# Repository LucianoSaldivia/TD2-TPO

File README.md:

# TD2-TPO
 Proyecto Emulador de Chip8 para Técnicas Digitales 2

|          Tarea           | Responsable  | Estado |
|:-------------------------|:------------:|:------:|
|        Diseño PCB        |  LL y Willy  |   -    |
|      Diseño Carcaza      |     Fran     |   -    |
|         Pantalla         |      LL      |   -    |
|            SD            |    Luchos    |   -    |
|      Instrucciones       | Fran, Luchos |   +    |
|          Armado          |      LL      |   -    |
|     TDS y estructura     |      LS      |   T    |
|      Documentacion       |  el guilardo |   -    |
| Interfaz seleccion juego |    Luchos    |   -    |

- Estados de Tareas:
  - "-"	-> Tarea en proceso
  - "+"	-> Tarea codeada, no testeada	
  - "T"	-> Tarea testeada, no integrada
  - "I"	-> Tarea integrada

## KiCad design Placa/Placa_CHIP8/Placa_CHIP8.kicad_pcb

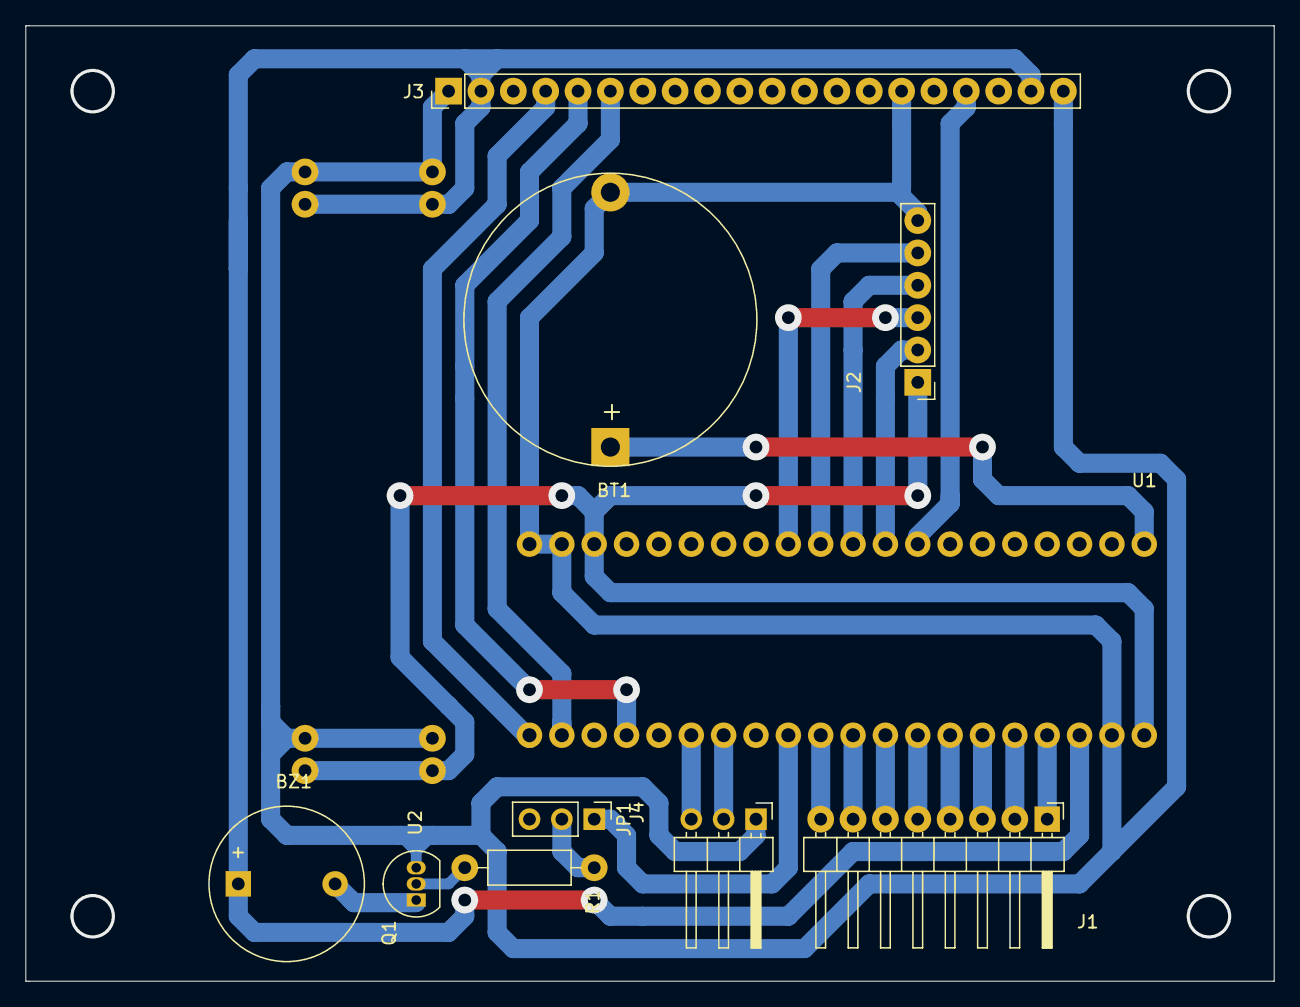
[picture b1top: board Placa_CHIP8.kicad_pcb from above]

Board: 2 copper layers, 98.0 x 75.0 mm, 11 parts (0 on the bottom side), 26 nets.

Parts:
BT1: Battery_Holder_CR2032; BatteryHolder_Keystone_103_1x20mm
BZ1: Buzzer; Buzzer_12x9.5RM7.6
J1: Conn_01x08_Male-Teclado-Matricial; PinHeader_1x08_P2.54mm_Horizontal
J2: Conn_01x06_Female-SD; PinHeader_1x06_P2.54mm_Vertical
J3: Conn_01x20_Female_LCD; PinHeader_1x20_P2.54mm_Vertical
J4: Conn_01x03_Male-UART; PinHeader_1x03_P2.54mm_Horizontal
JP1: Jumper; PinHeader_1x03_P2.54mm_Vertical
Q1: BC337; TO-92_Inline
R1: 10KΩ; R_Axial_DIN0207_L6.3mm_D2.5mm_P10.16mm_Horizontal
U1: STM32F103C8Tx; Blue_Pill
U2: Fuente

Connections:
+3V3: J2.1, U1.18, U1.40, U2.1
+5V: BZ1.1, J3.2, J3.19, U1.38, U2.3
+BATT: BT1.1, U1.1
/Buzzer: JP1.1, U1.29
/C1: J1.5, U1.33
/C2: J1.6, U1.32
/C3: J1.7, U1.31
/C4: J1.8, U1.30
/F1: J1.1, U1.37
/F2: J1.2, U1.36
/F3: J1.3, U1.35
/F4: J1.4, U1.34
/LCD_CLK: J3.6, U1.22
/LCD_CS: J3.4, U1.21
/LCD_MOSI: J3.5, U1.24
/LCD_RST: J3.17, U1.8
/RX_1: J4.2, U1.27
/SD_CLK: J2.4, U1.10
/SD_CS: J2.2, U1.9
/SD_MISO: J2.5, U1.11
/SD_MOSI: J2.3, U1.12
/TX_1: J4.3, U1.26
GND: BT1.2, J2.6, J3.1, J3.15, J3.20, J4.1, Q1.3, U1.19, U1.20, U1.39, U2.2, U2.4
unnamed: BZ1.2, Q1.1
unnamed: JP1.2, R1.2
unnamed: Q1.2, R1.1

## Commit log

2021-09-04 Primer Commit - Repo mudado
2021-09-05 [No testeado] Scheduler implementado como "objeto"
2021-09-07 Scheduler Testeado con dos tareas de ejemplo
    Se configuran las tareas con Período (en Ciclos Secundarios) y Offset (en micro segundos).
    Las tareas deben tener como parámetro void*, ejemplo:
    <task_type> <task_name>( void *p );
2021-09-15 Tareas / Responsables
2021-09-15 CHIP8 e instrucciones
    Implementacion de la estructura del CHIP8 y las instrucciones asociadas al mismo
2021-09-15 Estados de tareas
2021-09-15 Estado de Tareas -> Formato
2021-09-16 LCD GRAFICO & SD
    LCD grafico andando bien
    SD compila ok falta probar con una sd porque no tengo todavia
    Hay que cambiar SPI1 a SPI2
    Verificar TDS
2021-09-20 Agrego LCD Grafico, Teclado matricial y SD
    LCD GRAFICO OK -> Funcionando TIM4
    TECLADO MATRICIAL OK
    SD-> Resolviendo mis problemas con alarcon
2021-09-20 Cambio de lugar algunas cosas
2021-09-21 Agrego proyecto SD - Esta andando
2021-09-23 Agrego Intento de CHIP8
2021-09-23 Agrego configuracion HWD CHIP 8
2021-09-23 Terminar de resolver tema pantalla
2021-09-23 Graficar()->Andando
    Habría que probarla con una rom posta
2021-09-25 Agrego SD a CHIP 8
2021-10-06 graficando y leyendo de la SD
2021-10-06 Agrego placa - Lucho L & incios del gabinete
2021-10-07 Corriendo space invaders en resolucion nativa.
    Hay que mejorar la entrada de datos
    Resolucion de pantalla
2021-10-08 Anda un toque mejor
2021-10-18 SPI por HWD display
2021-10-21 Modifico Placa con las conexiones nuevas
2021-10-22 modif
2021-10-22 Agergo comprimido placa
2021-10-22 Funcionando mas decentemenete (CREO)
2021-10-25 cambios menores
2021-10-31 Agrego modelo Willy funcando ok y V1 gabinete
2021-11-10 Mejoras minimas codigo
2021-11-10 chip8 scheduler
2021-11-11 modificaciones proy tds
2021-11-23 codigo emprolijado
2021-11-23 Cambios menores en el codigo
2021-11-24 asd
    as
2021-11-24 Modifique instruccion cls
2021-12-08 Proyecto Aprobado
